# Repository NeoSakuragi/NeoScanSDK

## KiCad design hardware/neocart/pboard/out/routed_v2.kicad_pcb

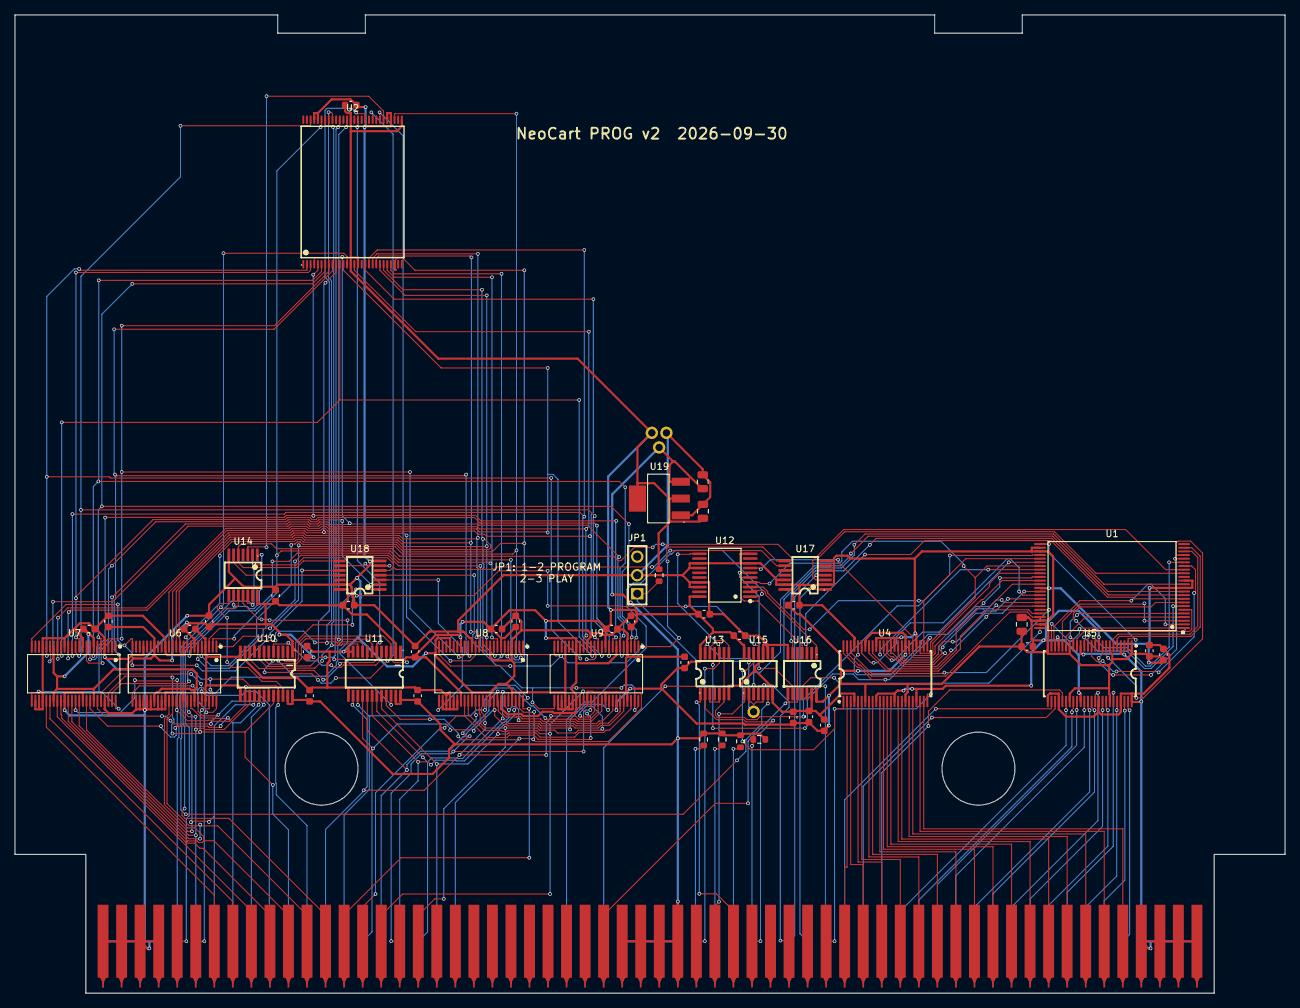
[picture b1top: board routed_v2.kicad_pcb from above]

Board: 2 copper layers, 174.0 x 134.0 mm, 58 parts (1 on the bottom side), 172 nets.

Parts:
C1, C2, C3: 10u; C_0805_2012Metric
C4, C5, C6, C7, C8, C9, C10, C11, C12, C13, C14, C15, C16, C17, C18, C19, C20, C21, C22, C23, C24, C25, C26, C27, C28: 100n; C_0603_1608Metric
J1: NeoGeo MVS Prog B Side Edge; neogeo-mvs-prog-b-side-edge
J2: NeoGeo MVS Prog A Side Edge; neogeo-mvs-prog-a-side-edge
JP1: MODE; HDR-TH_03P-P2.54-V-M
R1, R2, R3, R4, R5: 10k; R_0603_1608Metric
TP1: GND; TP_PTH_1.0
TP2: P3V3; TP_PTH_1.0
TP3: VCC5; TP_PTH_1.0
TP4: nPROG; TP_PTH_1.0
U1: S29GL064N; TSOP-48_L12.0-W18.4-P0.50-LS20.0-BL
U2: S29GL128P; TSOP-56_L18.4-W14.0-P0.50-LS20.0-TL
U4, U5: SN74LVC16245A; TSSOP-48_L12.5-W6.1-P0.50-LS8.1-BL
U6, U7, U8, U9: 74LVC16374A; TSSOP-48_L12.6-W6.2-P0.50-LS8.1-BL
U10, U11: 74LVC8T245; TSSOP-24_L7.8-W4.4-P0.65-LS6.4-BL
U12: SN74AHC273; SSOP-20_L7.5-W5.2-P0.65-LS8.0-BL
U13, U14: SN74LVC08A; TSSOP-14_L5.0-W4.4-P0.65-LS6.4-BL
U15, U16, U17: 74LVC32A; TSSOP-14_L5.0-W4.4-P0.65-LS6.4-BL
U18: SN74LVC04A; TSSOP-14_L5.0-W4.4-P0.65-LS6.4-BL
U19: AMS1117-3.3; SOT-223-3_L6.5-W3.4-P2.30-LS7.0-BR

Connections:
A1: J1.5 (A1), U5.47
A2: J1.6 (A2), U5.46
A3: J1.7 (A3), U5.44
A4: J1.8 (A4), U5.43
A5: J1.9 (A5), U5.41
A6: J1.10 (A6), U5.40
A7: J1.11 (A7), U5.38
A8: J1.12 (A8), U5.37
A9: J1.13 (A9), U5.36
A10: J1.14 (A10), U5.35
A11: J1.15 (A11), U5.33
A12: J1.16 (A12), U5.32
A13: J1.17 (A13), U5.30
A14: J1.18 (A14), U5.29
A15: J1.19 (A15), U5.27
A16: J1.20 (A16), U5.26
A17: J1.21 (A17), U16.12
A18: J1.22 (A18), U17.1
A19: J1.23 (A19), U17.4
BANK0: U12.2, U16.1
BANK1: U12.5, U16.4
BANK2: U12.6, U16.9
D0: J2.5 (D0), U4.23
D1: J2.6 (D1), U4.22
D2: J2.7 (D2), U4.20
D3: J2.8 (D3), U4.19
D4: J2.9 (D4), U4.17
D5: J2.10 (D5), U4.16
D6: J2.11 (D6), U4.14
D7: J2.12 (D7), U4.13
D8: J2.13 (D8), U4.12
D9: J2.14 (D9), U4.11
D10: J2.15 (D10), U4.9
D11: J2.16 (D11), U4.8
D12: J2.17 (D12), U4.6
D13: J2.18 (D13), U4.5
D14: J2.19 (D14), U4.3
D15: J2.20 (D15), U4.2
FA0: U1.25, U5.2
FA1: U1.24, U5.3
FA2: U1.23, U5.5
FA3: U1.22, U5.6
FA4: U1.21, U5.8
FA5: U1.20, U5.9
FA6: U1.19, U5.11
FA7: U1.18, U5.12
FA8: U1.8, U5.13
FA9: U1.7, U5.14
FA10: U1.6, U5.16
FA11: U1.5, U5.17
FA12: U1.4, U5.19
FA13: U1.3, U5.20
FA14: U1.2, U5.22
FA15: U1.1, U5.23
FA16: U1.48, U16.11
FA17: U1.17, U17.3
FA18: U1.16, U17.6
FA19: U1.9, U16.3
FA20: U1.10, U16.6
FA21: U1.13, U16.8
FD0: U1.29, U4.26, U12.3
FD1: U1.31, U4.27, U12.4
FD2: U1.33, U4.29, U12.7
FD3: U1.35, U4.30
FD4: U1.38, U4.32
FD5: U1.40, U4.33
FD6: U1.42, U4.35
FD7: U1.44, U4.36
FD8: U1.30, U4.37
FD9: U1.32, U4.38
FD10: U1.34, U4.40
FD11: U1.36, U4.41
FD12: U1.39, U4.43
FD13: U1.41, U4.44
FD14: U1.43, U4.46
FD15: U1.45, U4.47
GND: C1.2, C2.2, C3.2, C4.2, C5.2, C6.2, C7.2, C8.2, C9.2, C10.2, C11.2, C12.2, C13.2, C14.2, C15.2, C16.2, C17.2, C18.2, C19.2, C20.2, C21.2, C22.2, C23.2, C24.2, C25.2, C26.2, C27.2, C28.2, J1.1 (GND), J1.2 (GND), J1.3 (GND), J1.4 (GND), J1.57 (GND), J1.58 (GND), J1.59 (GND), J1.60 (GND), J2.1 (GND), J2.2 (GND), J2.3 (GND), J2.4 (GND), J2.57 (GND), J2.58 (GND), J2.59 (GND), J2.60 (GND), JP1.2, TP1.1, U1.26, U1.27, U1.46, U2.32, U2.33, U2.52, U2.53, U4.4, U4.10, U4.15, U4.21, U4.28, U4.34, U4.39, U4.45, U5.4, U5.10, U5.15, U5.21, U5.25, U5.28, U5.34, U5.39, U5.45, U5.48, U6.4, U6.10, U6.15, U6.21, U6.26, U6.27, U6.28, U6.29, U6.30, U6.32, U6.33, U6.34, U6.39, U6.45, U7.4, U7.10, U7.15, U7.21, U7.26, U7.27, U7.28, U7.34, U7.39, U7.45, U8.4, U8.10, U8.15, U8.21, U8.26, U8.27, U8.28, U8.29, U8.30, U8.34, U8.39, U8.45, U9.4, U9.10, U9.15, U9.21, U9.26, U9.27, U9.28, U9.29, U9.30, U9.34, U9.39, U9.45, U10.11, U10.12, U10.13, U11.11, U11.12, U11.13, U12.8, U12.10, U12.13, U12.14, U12.17, U12.18, U13.7, U14.7, U15.7, U15.9, U15.10, U16.7, U16.13, U17.2, U17.5, U17.7, U17.12, U17.13, U18.7, U18.13, U19.1
P3V3: C2.1, C3.1, C4.1, C5.1, C6.1, C7.1, C8.1, C9.1, C10.1, C11.1, C12.1, C13.1, C14.1, C15.1, C16.1, C17.1, C18.1, C19.1, C20.1, C21.1, C22.1, C23.1, C24.1, C25.1, C27.1, R1.2, TP2.1, U1.12, U1.14, U1.37, U1.47, U2.14, U2.16, U2.29, U2.43, U4.7, U4.18, U4.31, U4.42, U5.1, U5.7, U5.18, U5.24, U5.31, U5.42, U6.7, U6.18, U6.31, U6.42, U7.7, U7.18, U7.31, U7.42, U8.7, U8.18, U8.31, U8.42, U9.7, U9.18, U9.31, U9.42, U10.1, U11.1, U11.2, U12.20, U13.14, U14.14, U15.14, U16.14, U17.14, U18.14, U19.2, U19.4
PDLY: U14.5, U17.10, U18.8
RW: J2.21 (R/W), U4.1, U4.24, U15.12
SDPA8: J2.43 (SDPA8), U8.36, U9.36
SDPA9: J2.44 (SDPA9), U8.35, U9.35
SDPA10: J2.45 (SDPA10), U8.33, U9.33
SDPA11: J2.46 (SDPA11), U8.32, U9.32
SDPAD0: J1.41 (SDPAD0), U8.47, U9.47, U11.21
SDPAD1: J1.42 (SDPAD1), U8.46, U9.46, U11.20
SDPAD2: J1.43 (SDPAD2), U8.44, U9.44, U11.19
SDPAD3: J1.44 (SDPAD3), U8.43, U9.43, U11.18
SDPAD4: J1.45 (SDPAD4), U8.41, U9.41, U11.17
SDPAD5: J1.46 (SDPAD5), U8.40, U9.40, U11.16
SDPAD6: J1.47 (SDPAD6), U8.38, U9.38, U11.15
SDPAD7: J1.48 (SDPAD7), U8.37, U9.37, U11.14
SDPMPX: J2.47 (SDPMPX), U8.25, U8.48, U18.3
SDPOE_I: U18.6, U18.9
SDRA8: J2.49 (SDRA8), U6.36, U7.36
SDRA9: J2.50 (SDRA9), U6.35, U7.35
SDRA20: J2.51 (SDRA20), U7.33
SDRA21: J2.52 (SDRA21), U7.32
SDRA22: J2.53 (SDRA22), U7.30
SDRA23: J2.54 (SDRA23), U7.29
SDRAD0: J1.49 (SDRAD0), U6.47, U7.47, U10.21
SDRAD1: J1.50 (SDRAD1), U6.46, U7.46, U10.20
SDRAD2: J1.51 (SDRAD2), U6.44, U7.44, U10.19
SDRAD3: J1.52 (SDRAD3), U6.43, U7.43, U10.18
SDRAD4: J1.53 (SDRAD4), U6.41, U7.41, U10.17
SDRAD5: J1.54 (SDRAD5), U6.40, U7.40, U10.16
SDRAD6: J1.55 (SDRAD6), U6.38, U7.38, U10.15
SDRAD7: J1.56 (SDRAD7), U6.37, U7.37, U10.14
SDRMPX: J2.55 (SDRMPX), U6.25, U6.48, U18.1
VCC5: C1.1, C26.1, C28.1, J1.29 (VCC), J1.30 (VCC), J1.31 (VCC), J1.32 (VCC), J2.29 (VCC), J2.30 (VCC), J2.31 (VCC), J2.32 (VCC), R2.2, R3.2, R4.2, R5.2, TP3.1, U10.23, U10.24, U11.23, U11.24, U19.3
VDIR: U10.2, U15.11
V_ADR0: U2.51, U6.2, U8.2
V_ADR1: U2.31, U6.3, U8.3
V_ADR2: U2.26, U6.5, U8.5
V_ADR3: U2.25, U6.6, U8.6
V_ADR4: U2.24, U6.8, U8.8
V_ADR5: U2.23, U6.9, U8.9
V_ADR6: U2.22, U6.11, U8.11
V_ADR7: U2.21, U6.12, U8.12
V_ADR8: U2.20, U6.13, U8.13
V_ADR9: U2.10, U6.14, U8.14
V_ADR10: U2.9, U7.2, U8.16
V_ADR11: U2.8, U7.3, U8.17
V_ADR12: U2.7, U7.5, U9.2
V_ADR13: U2.6, U7.6, U9.3
V_ADR14: U2.5, U7.8, U9.5
V_ADR15: U2.4, U7.9, U9.6
V_ADR16: U2.3, U7.11, U9.8
V_ADR17: U2.54, U7.12, U9.9
V_ADR18: U2.19, U7.13, U9.11
V_ADR19: U2.18, U7.14, U9.12
V_ADR20: U2.11, U7.16, U9.13
V_ADR21: U2.12, U7.17, U9.14
V_ADR22: U2.15, U7.19, U9.16
V_ADR23: U2.2, U7.20, U9.17
V_DQ0: U2.35, U10.3, U11.3
V_DQ1: U2.37, U10.4, U11.4
V_DQ2: U2.39, U10.5, U11.5
V_DQ3: U2.41, U10.6, U11.6
V_DQ4: U2.44, U10.7, U11.7
V_DQ5: U2.46, U10.8, U11.8
V_DQ6: U2.48, U10.9, U11.9
V_DQ7: U2.50, U10.10, U11.10
nASEL_OE: U6.1, U6.24, U7.1, U7.24, U18.10
nBSEL_OE: U8.1, U8.24, U9.1, U9.24, U17.8
nPDTACK: J1.28 (PDTACK), R5.1
nPMPX: U9.25, U9.48, U18.4
nPOE_BOTH: U14.6, U18.11
nPORTADRS: J2.33 (PORTADRS), U16.2, U16.5, U16.10
nPORTOE: U13.3, U13.5
nPORTOEL: J2.26 (PORTOEL), U13.1
nPORTOEU: J2.25 (PORTOEU), U13.2
nPORTWEL: J2.28 (PORTWEL), U12.11, U13.10
nPORTWEU: J2.27 (PORTWEU), U15.1
nPROG: JP1.1, R1.1, TP4.1, U15.2, U15.5, U15.13
nPWAIT0: J1.26 (PWAIT0), R3.1
nPWAIT1: J1.27 (PWAIT1), R4.1
nP_OE: U1.28, U13.6, U13.9
nP_WE: U1.11, U13.13, U15.3
nRESET: J1.35 (RESET), U12.1
nRMPX: U7.25, U7.48, U18.2
nROMOE: J1.33 (ROMOE), U13.4
nROMOEU: J2.23 (ROMOEU), U15.4
nROMWAIT: J1.25 (ROMWAIT), R2.1
nSDPOE: J2.48 (SDPOE), U14.2, U14.4, U14.12, U14.13, U17.9, U18.5
nSDROE: J2.56 (SDROE), U14.1, U14.9
nVA_BUFOE: U10.22, U14.8
nVB_BUFOE: U11.22, U14.11
nV_OE: U2.34, U14.3
nV_WE: U2.13, U14.10, U15.6
nXCVR_EN: U4.25, U4.48, U13.11
nXEN1: U13.8, U13.12

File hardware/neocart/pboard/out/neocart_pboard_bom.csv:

Comment,Designator,Footprint,LCSC Part #
100n,"C23,C5,C17,C15,C16,C26,C19,C22,C27,C8,C14,C21,C18,C28,C6,C4,C12,C9,C25,C7,C11,C20,C10,C24,C13",C0603,C14663
74LVC16245A,"U5,U4",TSSOP-48_L12.5-W6.1-P0.50-LS8.1-BL,C548160
74LVC8T245,"U11,U10",TSSOP-24_L7.8-W4.4-P0.65-LS6.4-BL,C458788
10k,"R3,R1,R5,R2,R4",R0603,C25804
74LVC08A,"U13,U14",TSSOP-14_L5.0-W4.4-P0.65-LS6.4-BL,C6053
74LVC32A,"U17,U16,U15",TSSOP-14_L5.0-W4.4-P0.65-LS6.4-BL,C6087
74LVC16374A,"U9,U8,U7,U6",TSSOP-48_L12.6-W6.2-P0.50-LS8.1-BL,C6074
10u,"C2,C3,C1",C0805,C15850
SN74AHC273,U12,SSOP-20_L7.5-W5.2-P0.65-LS8.0-BL,C2877489
S29GL064N,U1,TSOP-48_L12.0-W18.4-P0.50-LS20.0-BL,C117907
S29GL128P,U2,TSOP-56_L18.4-W14.0-P0.50-LS20.0-TL,C914939
SN74LVC04A,U18,TSSOP-14_L5.0-W4.4-P0.65-LS6.4-BL,C352968
AMS1117-3.3,U19,SOT-223-3_L6.5-W3.4-P2.30-LS7.0-BR,C6186

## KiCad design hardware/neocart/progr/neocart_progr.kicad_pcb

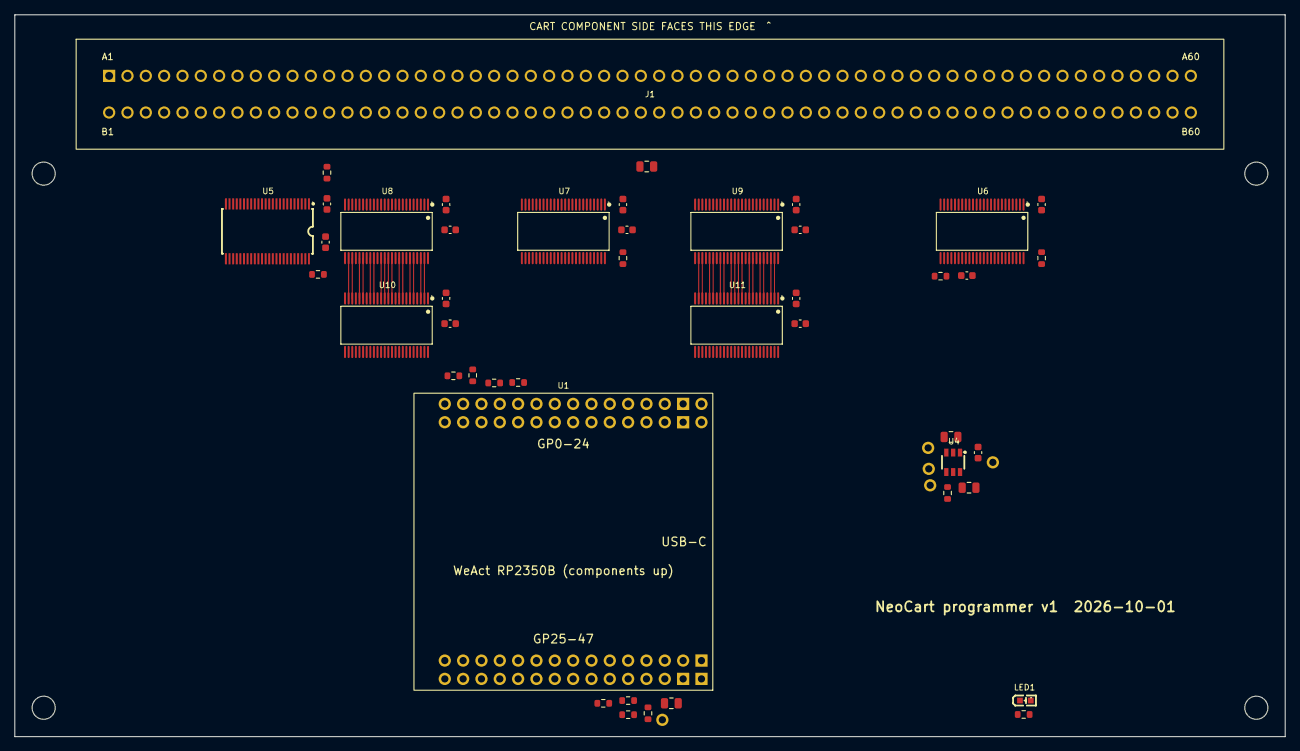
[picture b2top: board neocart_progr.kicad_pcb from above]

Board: 2 copper layers, 176.0 x 100.0 mm, 54 parts (0 on the bottom side), 167 nets.

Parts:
C1, C3, C4, C5: 10u; C_0805_2012Metric
C2, C6, C7, C8, C9, C10, C11, C12, C13, C14, C15, C16, C17, C18, C19: 100n; C_0603_1608Metric
J1: MVS slot; MVS_SLOT_EDAC_345-120
LED1: CART; LED-SMD_L1.6-W0.8-R-RD
MH1, MH2, MH3, MH4: M3; MH_M3
R1, R2, R3, R4, R5, R6, R7, R9, R10: 10k; R_0603_1608Metric
R8: 33k; R_0603_1608Metric
R11, R12, R13, R14, R15: 1k; R_0603_1608Metric
TP1: GND; TP_PTH_1.0
TP2: P3V3; TP_PTH_1.0
TP3: VCART; TP_PTH_1.0
TP4: VBUS; TP_PTH_1.0
TP5: GPIO47; TP_PTH_1.0
U1: WeAct RP2350B; WEACT_RP2350B_CORE
U4: TPS2553; SOT-23-6_L2.9-W1.6-P0.95-LS2.8-BR
U5: 74LVC16245A; TSSOP-48_L12.5-W6.1-P0.50-LS8.1-BL
U6, U7, U8, U9: SN74LVC16T245; TSSOP-48_L12.6-W6.2-P0.50-LS8.1-BL
U10, U11: 74LVC16374A; TSSOP-48_L12.6-W6.2-P0.50-LS8.1-BL

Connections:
A1: J1.B5, U8.2
A2: J1.B6, U8.3
A3: J1.B7, U8.5
A4: J1.B8, U8.6
A5: J1.B9, U8.8
A6: J1.B10, U8.9
A7: J1.B11, U8.11
A8: J1.B12, U8.12
A9: J1.B13, U8.13
A10: J1.B14, U8.14
A11: J1.B15, U8.16
A12: J1.B16, U8.17
A13: J1.B17, U8.19
A14: J1.B18, U8.20
A15: J1.B19, U8.22
A16: J1.B20, U8.23
A17: J1.B21, U9.2
A18: J1.B22, U9.3
A19: J1.B23, U9.5
CLK4M: J1.B34, U9.22
CLK68K: J1.B24, U7.22
D0: J1.A5, U5.2
D1: J1.A6, U5.3
D2: J1.A7, U5.5
D3: J1.A8, U5.6
D4: J1.A9, U5.8
D5: J1.A10, U5.9
D6: J1.A11, U5.11
D7: J1.A12, U5.12
D8: J1.A13, U5.13
D9: J1.A14, U5.14
D10: J1.A15, U5.16
D11: J1.A16, U5.17
D12: J1.A17, U5.19
D13: J1.A18, U5.20
D14: J1.A19, U5.22
D15: J1.A20, U5.23
GND: C1.2, C2.2, C3.2, C4.2, C5.2, C6.2, C7.2, C8.2, C9.2, C10.2, C11.2, C12.2, C13.2, C14.2, C15.2, C16.2, C17.2, C18.2, C19.2, J1.A1, J1.A2, J1.A3, J1.A4, J1.A57, J1.A58, J1.A59, J1.A60, J1.B1, J1.B2, J1.B3, J1.B4, J1.B57, J1.B58, J1.B59, J1.B60, R5.2, R6.2, R8.2, R10.2, R15.2, TP1.1, U1.BI2, U1.BO2, U1.TI1, U1.TO1, U1.TO2, U4.2, U5.4, U5.10, U5.15, U5.21, U5.28, U5.34, U5.39, U5.45, U6.4, U6.10, U6.15, U6.21, U6.28, U6.34, U6.39, U6.45, U7.4, U7.10, U7.15, U7.21, U7.26, U7.28, U7.34, U7.39, U7.45, U8.4, U8.10, U8.15, U8.21, U8.28, U8.34, U8.39, U8.45, U9.4, U9.10, U9.15, U9.21, U9.28, U9.34, U9.39, U9.45, U10.1, U10.4, U10.10, U10.15, U10.21, U10.24, U10.28, U10.34, U10.39, U10.45, U11.1, U11.4, U11.10, U11.15, U11.21, U11.24, U11.28, U11.34, U11.39, U11.45
GPIO47: TP5.1, U1.TI4
G_CLK68K: U1.TO8, U7.27
G_RW: U1.TO15, U7.47
G_SDPMPX: U1.TO9, U7.30
G_SDRMPX: U1.TO10, U7.33
G_nAS: U1.TI14, U7.46
G_nPORTADRS: U1.TI10, U7.35
G_nPORTOEL: U1.TO12, U7.38
G_nPORTOEU: U1.TI12, U7.40
G_nPORTWEL: U1.TO11, U7.36
G_nPORTWEU: U1.TI11, U7.37
G_nROMOE: U1.TO14, U7.44
G_nROMOEL: U1.TO13, U7.41
G_nROMOEU: U1.TI13, U7.43
G_nSDPOE: U1.TI8, U7.29
G_nSDROE: U1.TI9, U7.32
ILIM: R8.1, U4.5
LCLK1: U1.TO7, U10.25, U10.48
LCLK2: U1.TI6, U11.25, U11.48
LED1_K: LED1.2, R15.1
L_A1: U8.47, U10.2
L_A2: U8.46, U10.3
L_A3: U8.44, U10.5
L_A4: U8.43, U10.6
L_A5: U8.41, U10.8
L_A6: U8.40, U10.9
L_A7: U8.38, U10.11
L_A8: U8.37, U10.12
L_A9: U8.36, U10.13
L_A10: U8.35, U10.14
L_A11: U8.33, U10.16
L_A12: U8.32, U10.17
L_A13: U8.30, U10.19
L_A14: U8.29, U10.20
L_A15: U8.27, U10.22
L_A16: U8.26, U10.23
L_A17: U9.47, U11.2
L_A18: U9.46, U11.3
L_A19: U9.44, U11.5
L_CLK4M: U9.27, U11.22
L_SDPA8: U9.35, U11.14
L_SDPA9: U9.33, U11.16
L_SDPA10: U9.32, U11.17
L_SDPA11: U9.30, U11.19
L_SDRA8: U9.43, U11.6
L_SDRA9: U9.41, U11.8
L_SDRA20: U9.40, U11.9
L_SDRA21: U9.38, U11.11
L_SDRA22: U9.37, U11.12
L_SDRA23: U9.36, U11.13
L_nRESET: U9.29, U11.20
L_nSLOTCS: U9.26, U11.23
MD0: U1.BI3, U5.47, U6.47, U10.47, U11.47
MD1: U1.BO4, U5.46, U6.46, U10.46, U11.46
MD2: U1.BI4, U5.44, U6.44, U10.44, U11.44
MD3: U1.BO5, U5.43, U6.43, U10.43, U11.43
MD4: U1.BI5, U5.41, U6.41, U10.41, U11.41
MD5: U1.BO6, U5.40, U6.40, U10.40, U11.40
MD6: U1.BI6, U5.38, U6.38, U10.38, U11.38
MD7: U1.BO7, U5.37, U6.37, U10.37, U11.37
MD8: U1.BI7, U5.36, U6.36, U10.36, U11.36
MD9: U1.BO8, U5.35, U6.35, U10.35, U11.35
MD10: U1.BI8, U5.33, U6.33, U10.33, U11.33
MD11: U1.BO9, U5.32, U6.32, U10.32, U11.32
MD12: U1.BI9, U5.30, U6.30, U10.30, U11.30
MD13: U1.BO10, U5.29, U6.29, U10.29, U11.29
MD14: U1.BI10, U5.27, U6.27, U10.27, U11.27
MD15: U1.BO11, U5.26, U6.26, U10.26, U11.26
P3V3: C5.1, C6.1, C7.1, C8.1, C9.1, C10.1, C11.1, C12.1, C14.1, C16.1, C18.1, R1.2, R2.2, R3.2, R4.2, R7.2, TP2.1, U1.TI3, U1.TO3, U5.7, U5.18, U5.31, U5.42, U6.31, U6.42, U7.1, U7.24, U7.31, U7.42, U8.1, U8.24, U8.31, U8.42, U9.1, U9.24, U9.31, U9.42, U10.7, U10.18, U10.31, U10.42, U11.7, U11.18, U11.31, U11.42
RW: J1.A21, U7.2
SDPA8: J1.A43, U9.14
SDPA9: J1.A44, U9.16
SDPA10: J1.A45, U9.17
SDPA11: J1.A46, U9.19
SDPAD0: J1.B41, U6.13
SDPAD1: J1.B42, U6.14
SDPAD2: J1.B43, U6.16
SDPAD3: J1.B44, U6.17
SDPAD4: J1.B45, U6.19
SDPAD5: J1.B46, U6.20
SDPAD6: J1.B47, U6.22
SDPAD7: J1.B48, U6.23
SDPMPX: J1.A47, U7.19
SDRA8: J1.A49, U9.6
SDRA9: J1.A50, U9.8
SDRA20: J1.A51, U9.9
SDRA21: J1.A52, U9.11
SDRA22: J1.A53, U9.12
SDRA23: J1.A54, U9.13
SDRAD0: J1.B49, U6.2
SDRAD1: J1.B50, U6.3
SDRAD2: J1.B51, U6.5
SDRAD3: J1.B52, U6.6
SDRAD4: J1.B53, U6.8
SDRAD5: J1.B54, U6.9
SDRAD6: J1.B55, U6.11
SDRAD7: J1.B56, U6.12
SDRMPX: J1.A55, U7.16
S_nPDTACK: R14.2, U1.BO13
S_nPWAIT0: R12.2, U1.BO12
S_nPWAIT1: R13.2, U1.BI12
S_nROMWAIT: R11.2, U1.BI11
VBUS: C1.1, C2.1, TP4.1, U1.BO1, U4.1
VCART: C3.1, C4.1, C13.1, C15.1, C17.1, C19.1, J1.A29, J1.A30, J1.A31, J1.A32, J1.B29, J1.B30, J1.B31, J1.B32, LED1.1, R9.1, TP3.1, U4.6, U6.7, U6.18, U7.7, U7.18, U8.7, U8.18, U9.7, U9.18
VCART_EN: R6.1, U1.TO6, U4.3
VCART_SENSE: R9.2, R10.1, U1.TO5
XDIR: R5.1, U1.BI13, U5.1, U5.24, U6.1, U6.24
nAS: J1.A22, U7.3
nOE_D: R1.1, U1.BO14, U5.25, U5.48
nOE_OUT: R4.1, U1.TI7, U7.25, U7.48, U8.25, U8.48, U9.25, U9.48
nOE_VA: R2.1, U1.BI14, U6.48
nOE_VB: R3.1, U1.BI15, U6.25
nPDTACK: J1.B28, R14.1
nPORTADRS: J1.A33, U7.14
nPORTOEL: J1.A26, U7.11
nPORTOEU: J1.A25, U7.9
nPORTWEL: J1.A28, U7.13
nPORTWEU: J1.A27, U7.12
nPWAIT0: J1.B26, R12.1
nPWAIT1: J1.B27, R13.1
nRESET: J1.B35, U9.20
nROMOE: J1.B33, U7.5
nROMOEL: J1.A24, U7.8
nROMOEU: J1.A23, U7.6
nROMWAIT: J1.B25, R11.1
nSDPOE: J1.A48, U7.20
nSDROE: J1.A56, U7.17
nSLOTCS: J1.A42, U9.23
nVCART_FAULT: R7.1, U1.TI5, U4.4

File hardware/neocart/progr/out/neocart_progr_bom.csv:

Comment,Designator,Footprint,LCSC Part #
100n,"C12,C6,C11,C9,C18,C8,C2,C7,C19,C15,C10,C17,C16,C14,C13",C0603,C14663
10k,"R1,R2,R4,R9,R5,R6,R7,R10,R3",R0603,C25804
1k,"R15,R12,R14,R11,R13",R0603,C21190
CART,LED1,LED-SMD_L1.6-W0.8-R-RD,C2286
SN74LVC16T245,"U9,U6,U7,U8",TSSOP-48_L12.6-W6.2-P0.50-LS8.1-BL,C148170
TPS2553,U4,SOT-23-6_L2.9-W1.6-P0.95-LS2.8-BR,C55266
10u,"C3,C5,C4,C1",C0805,C15850
74LVC16245A,U5,TSSOP-48_L12.5-W6.1-P0.50-LS8.1-BL,C548160
74LVC16374A,"U10,U11",TSSOP-48_L12.6-W6.2-P0.50-LS8.1-BL,C6074
33k,R8,R0603,C4216
